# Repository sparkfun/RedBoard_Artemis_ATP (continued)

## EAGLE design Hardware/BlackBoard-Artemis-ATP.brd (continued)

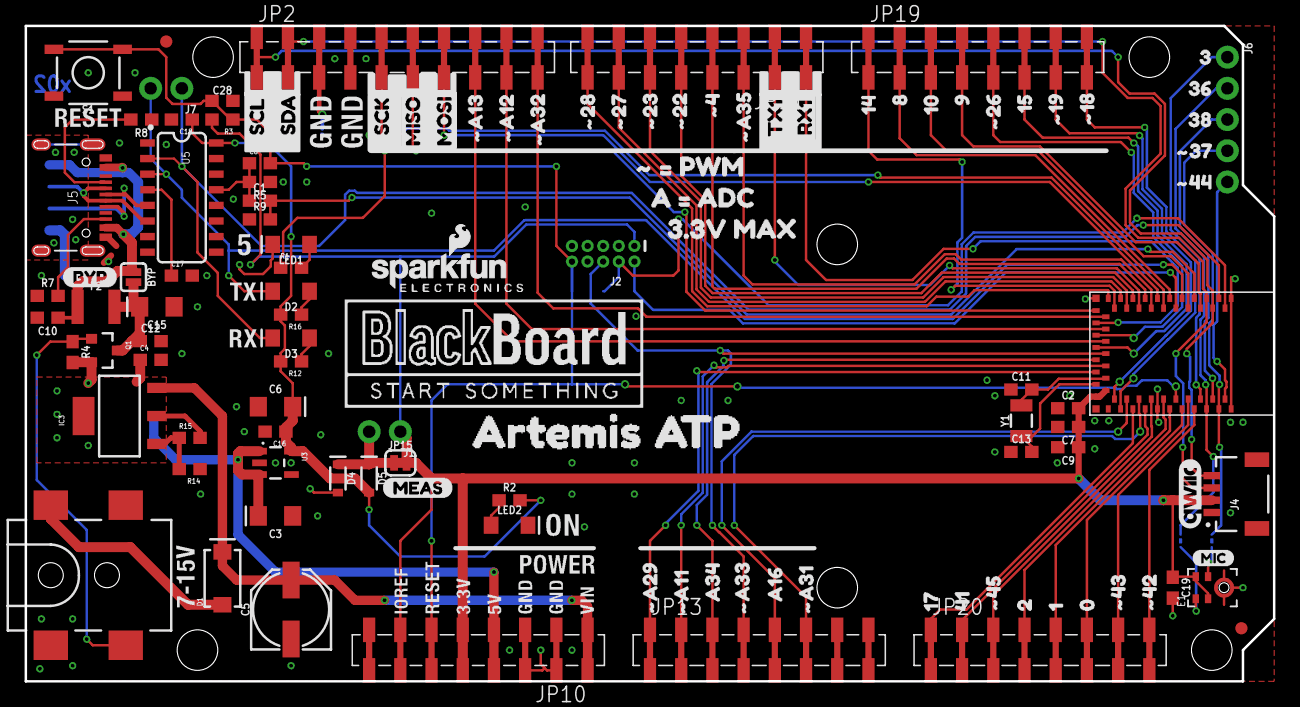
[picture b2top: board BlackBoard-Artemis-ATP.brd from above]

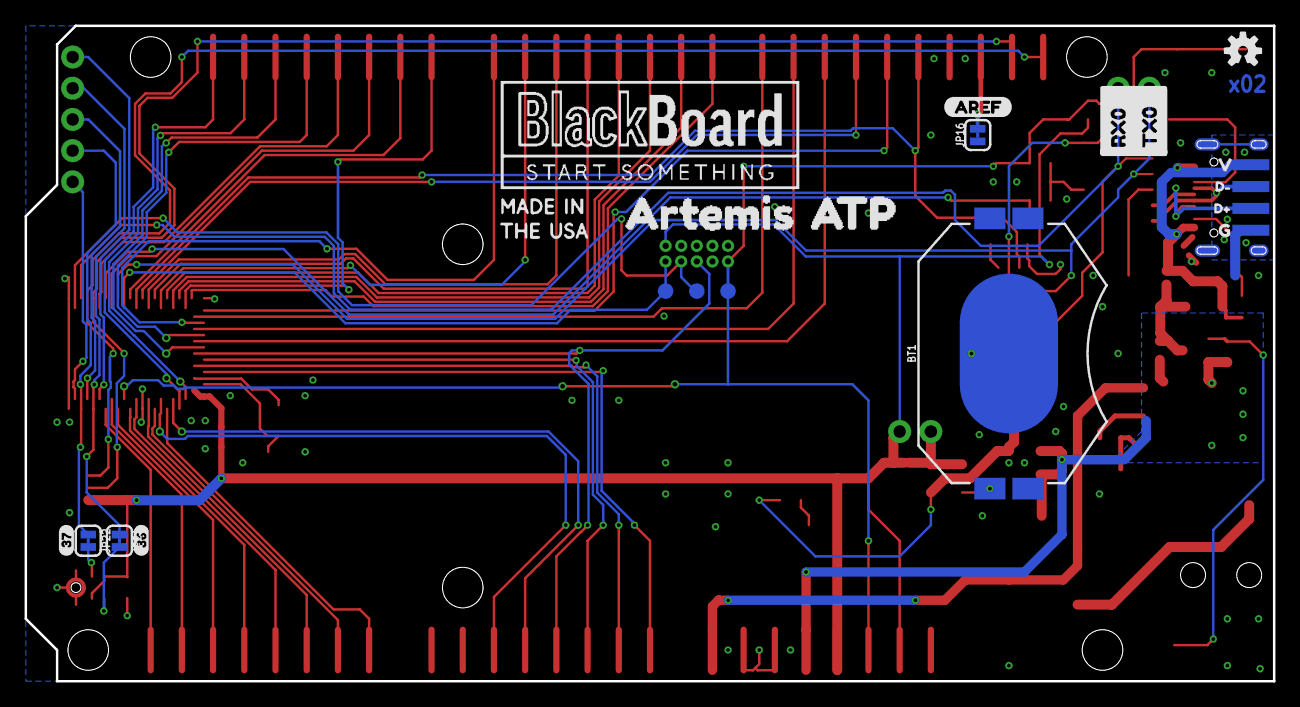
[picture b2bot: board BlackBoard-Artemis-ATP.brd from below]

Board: 2 copper layers, 101.6 x 53.3 mm, 149 parts (23 on the bottom side), 77 nets.

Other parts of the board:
JP17, JP18: STAND-OFF
U$1, U$3: BLACKBOARDLOGO#PNG
U$2: D#3
U$4: MADEINUSA#PNG
U$9: QWIIC_COPYRIGHT_SMALL
U$10: D#4
U$11: G1
U$12: V0
U$13: #A332
U$14, U$15: ARTEMIS0
U$17: A160
U$18: SCL1
U$19: #48
U$20: AREF2
U$21: #229
U$22: SDA0
U$23: #3711
U$24: #187
U$25: #2310
U$26: #2711
U$27: #2812
U$28, U$61: ATP1
U$29: #A113
U$30: #A294
U$31: #A310
U$32: #196
U$33: #A357
U$34: #A1214
U$35: #A1315
U$36: #A3213
U$37: #264
U$38: A342
U$39: #4213
U$40: #4314
U$41: #4412
U$42: #4518
U$43: 015
U$44: 38
U$45: 81
U$46: 93
U$47: MISO8
U$48: MOSI7
U$49: RX01
U$50: SCK9
U$51: 102
U$52: 116
U$53: TX00
U$54: 140
U$55: 155
U$56: 217
U$57: 369
U$58: 1720
U$59: 3810
U$60: 4119
U$62: MIC0
U$63: 364
U$64: 373
U$66: #_#_PWM7
U$67: 3#3V_MAX2
U$68: BYP0
U$69: A_#_ADC6
U$70: MEAS3
U$71: RX11
U$72: TX10

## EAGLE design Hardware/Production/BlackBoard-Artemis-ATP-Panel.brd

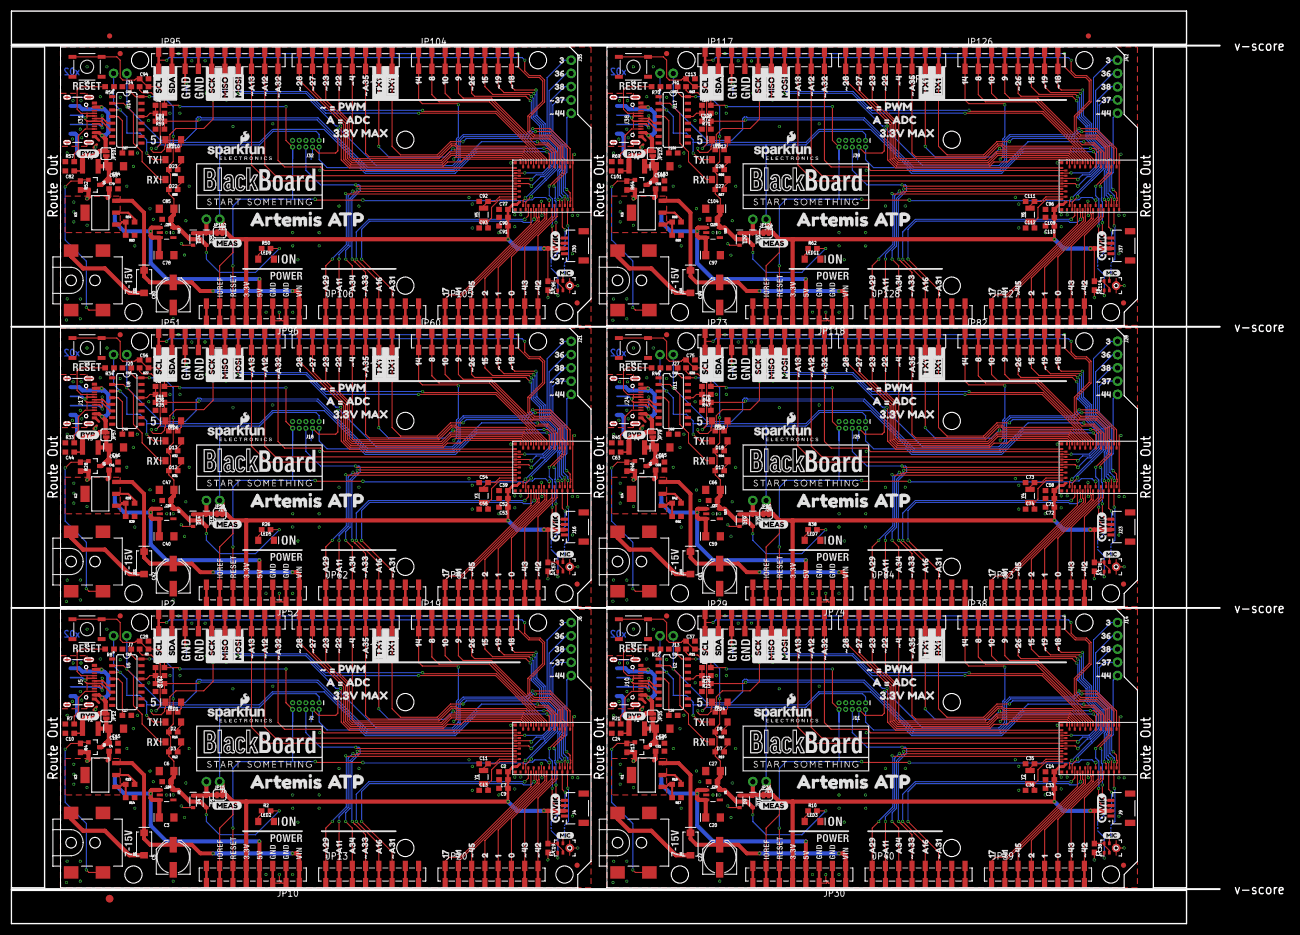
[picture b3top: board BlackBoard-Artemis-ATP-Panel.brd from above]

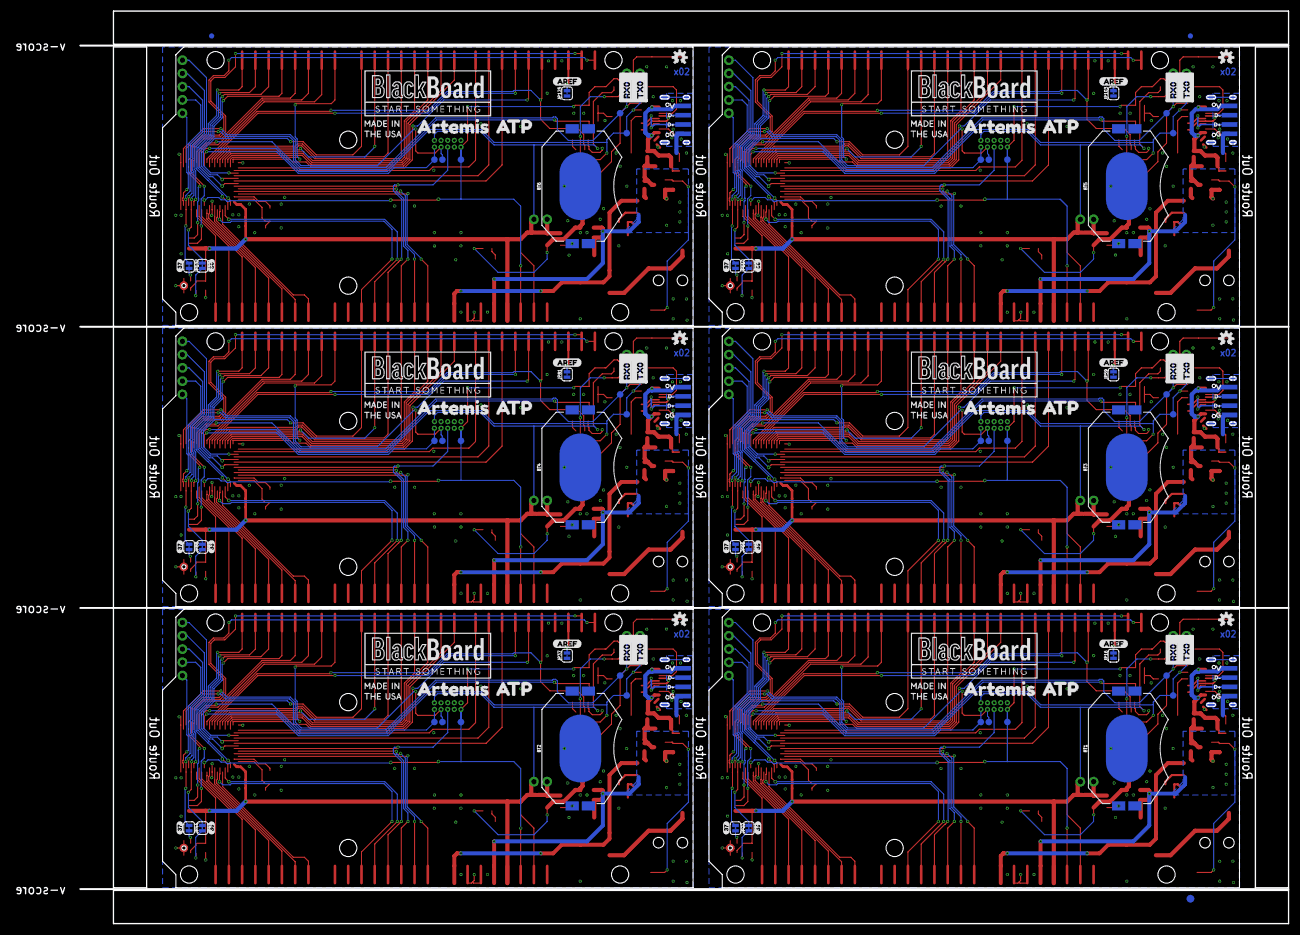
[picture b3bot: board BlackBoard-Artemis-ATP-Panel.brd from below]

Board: 2 copper layers, 244.6 x 174.6 mm, 906 parts (153 on the bottom side), 462 nets.

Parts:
BT1, BT2, BT3, BT4, BT5, BT6: CR2032; BATTCON_20MM_4LEGS_OVERPASTE
C1, C32, C51, C70, C89, C108: 2.2uF; 0603
C2, C4, C8, C10, C12, C14, C18, C19, C21, C23, C24, C25, C31, C38, C39, C41, C43, C44, C45, C50, C57, C58, C60, C62, C63, C64, C69, C76, C77, C79, C81, C82, C83, C88, C95, C96, C98, C100, C101, C102, C107, C114: 0.1uF; 0603
C3, C6, C15, C20, C26, C27, C40, C46, C47, C59, C65, C66, C78, C84, C85, C97, C103, C104: 10uF; EIA3216
C5, C22, C42, C61, C80, C99: 47uF; PANASONIC_D
C7, C33, C52, C71, C90, C109: 10uF; 0603
C9, C16, C29, C34, C48, C53, C67, C72, C86, C91, C105, C110: 1.0uF; 0603
C11, C13, C35, C36, C54, C55, C73, C74, C92, C93, C111, C112: 15pF; 0603
C17, C30, C49, C68, C87, C106: 10nF; 0603
C28, C37, C56, C75, C94, C113: 1nF; 0603
D1, D6, D11, D16, D21, D26: 1A/40V/500mV; SMA-DIODE
D2, D8, D13, D18, D23, D28: GREEN; LED-1206
D3, D7, D12, D17, D22, D27: Yellow; LED-1206
D4, D5, D9, D10, D14, D15, D19, D20, D24, D25, D29, D30: 1A/23V/620mV; SOD-323
E1, E2, E3, E4, E5, E6: SPH0641LM4H-1; SPH0641LM4H-1_MICROPHONE
E$1, E$2, E$3, E$4: FIDUCIAL-1X2
E$5, E$6: FIDUCIAL-1.5X3
F1, F2, F3, F4, F5, F6: 6V/2A; 1210
FRAME1, FRAME2, FRAME3, FRAME4, FRAME5, FRAME6: FRAME-LETTERNO_PACKAGE; DUMMY
IC1, IC2, IC3, IC4, IC5, IC6: LM1117; SOT223-ALT1
J1, J7, J12, J13, J19, J20, J26, J27, J33, J34, J40, J41: 1X02_NO_SILK
J2, J11, J18, J25, J32, J39: CORTEX_DEBUG; 2X5-PTH-1.27MM-NO_SILK
J3, J8, J15, J22, J29, J36: POWER_JACKTOE; POWER_JACK_SMD_OVERPASTE_TOE
J4, J9, J16, J23, J30, J37: JST04_1MM_RA
J5, J10, J17, J24, J31, J38: USB-C; USB-C-16P
J6, J14, J21, J28, J35, J42: 1X05_NO_SILK
JP1, JP31, JP53, JP75, JP97, JP119: SFE_LOGO_NAME.1_INCH; SFE_LOGO_NAME_.1
JP2, JP29, JP51, JP73, JP95, JP117: M10SMD_COMBO; 1X10_SMD_COMBINED
JP3, JP4, JP5, JP6, JP17, JP18, JP23, JP24, JP25, JP26, JP41, JP42, JP45, JP46, JP47, JP48, JP63, JP64, JP67, JP68, JP69, JP70, JP85, JP86, JP89, JP90, JP91, JP92, JP107, JP108, JP111, JP112, JP113, JP114, JP129, JP130: STAND-OFF
JP7, JP32, JP54, JP76, JP98, JP120: SFE_LOGO_FLAME.1_INCH; SFE_LOGO_FLAME_.1
JP8, JP9, JP27, JP28, JP49, JP50, JP71, JP72, JP93, JP94, JP115, JP116: FIDUCIAL1X2; FIDUCIAL-1X2
JP10, JP30, JP52, JP74, JP96, JP118: 1X08_SMD_COMBINED
JP11, JP13, JP19, JP20, JP33, JP38, JP39, JP40, JP55, JP60, JP61, JP62, JP77, JP82, JP83, JP84, JP99, JP104, JP105, JP106, JP121, JP126, JP127, JP128: JP11; 1X08_SMD_COMBINED
JP12, JP35, JP57, JP79, JP101, JP123: SMT-JUMPER_2_NO_SILK
JP14, JP34, JP56, JP78, JP100, JP122: USB_SOLDER_PADS; USB-SOLDER-PADS
JP15, JP16, JP21, JP22, JP36, JP37, JP43, JP44, JP58, JP59, JP65, JP66, JP80, JP81, JP87, JP88, JP102, JP103, JP109, JP110, JP124, JP125, JP131, JP132: SMT-JUMPER_2_NC_TRACE_SILK
LED1, LED4, LED6, LED8, LED10, LED12: BLUE; LED-1206
LED2, LED3, LED5, LED7, LED9, LED11: GREEN; LED-1206
Q1, Q2, Q3, Q4, Q5, Q6: 1.1A/60V/600mΩ; SOT23-3
R1, R6, R12, R16, R19, R20, R25, R31, R32, R37, R43, R44, R49, R55, R56, R61, R67, R68: 4.7k; 0603
R2, R4, R9, R10, R13, R23, R26, R28, R35, R38, R40, R47, R50, R52, R59, R62, R64, R71: 10k; 0603
R3, R5, R11, R24, R27, R36, R39, R48, R51, R60, R63, R72: 100k; 0603
R7, R8, R21, R22, R33, R34, R45, R46, R57, R58, R69, R70: 5.1k; 0603
R14, R17, R29, R41, R53, R65: 715; 0603
R15, R18, R30, R42, R54, R66: 240; 0603
S1, S2, S3, S4, S5, S6: TACTILE_SWITCH_SMD_5.2MM
TP1, TP2, TP3, TP4, TP7, TP10, TP11, TP12, TP15, TP16, TP17, TP20, TP21, TP22, TP25, TP26, TP27, TP30: PAD.03X.05
TP5, TP6, TP8, TP9, TP13, TP14, TP18, TP19, TP23, TP24, TP28, TP29: TEST-POINT3X5; PAD.03X.05
U1, U3, U7, U10, U13, U16: AP2112-3.3V; SOT23-5
U2, U5, U8, U11, U14, U17: CH340C; SO016
U4, U6, U9, U12, U15, U18: ARTEMIS_MODULESMD; ARTEMIS_FP
U$1, U$3, U$6, U$7, U$136, U$137, U$203, U$204, U$270, U$271, U$337, U$338: BLACKBOARDLOGO#PNG
U$2, U$75, U$142, U$209, U$276, U$343: D#3
U$4, U$8, U$138, U$205, U$272, U$339: MADEINUSA#PNG
U$5, U$16, U$135, U$202, U$269, U$336: OSHW-LOGOS; OSHW-LOGO-S
U$9, U$65, U$139, U$206, U$273, U$340: QWIIC_COPYRIGHT_SMALL
U$10, U$76, U$143, U$210, U$277, U$344: D#4
U$11, U$73, U$140, U$207, U$274, U$341: G1
U$12, U$74, U$141, U$208, U$275, U$342: V0
U$13, U$133, U$200, U$267, U$334, U$401: #A332
U$14, U$15, U$77, U$78, U$144, U$145, U$211, U$212, U$278, U$279, U$345, U$346: ARTEMIS0
U$17, U$79, U$146, U$213, U$280, U$347: A160
U$18, U$105, U$172, U$239, U$306, U$373: SCL1
U$19, U$80, U$147, U$214, U$281, U$348: #48
U$20, U$104, U$171, U$238, U$305, U$372: AREF2
U$21, U$81, U$148, U$215, U$282, U$349: #229
U$22, U$106, U$173, U$240, U$307, U$374: SDA0
U$23, U$110, U$177, U$244, U$311, U$378: #3711
U$24, U$107, U$174, U$241, U$308, U$375: #187
U$25, U$82, U$149, U$216, U$283, U$350: #2310
U$26, U$83, U$150, U$217, U$284, U$351: #2711
U$27, U$84, U$151, U$218, U$285, U$352: #2812
U$28, U$61, U$128, U$134, U$195, U$201, U$262, U$268, U$329, U$335, U$396, U$402: ATP1
U$29, U$85, U$152, U$219, U$286, U$353: #A113
U$30, U$86, U$153, U$220, U$287, U$354: #A294
U$31, U$87, U$154, U$221, U$288, U$355: #A310
U$32, U$108, U$175, U$242, U$309, U$376: #196
U$33, U$88, U$155, U$222, U$289, U$356: #A357
U$34, U$89, U$156, U$223, U$290, U$357: #A1214
U$35, U$90, U$157, U$224, U$291, U$358: #A1315
U$36, U$91, U$158, U$225, U$292, U$359: #A3213
U$37, U$109, U$176, U$243, U$310, U$377: #264
U$38, U$92, U$159, U$226, U$293, U$360: A342
U$39, U$111, U$178, U$245, U$312, U$379: #4213
U$40, U$112, U$179, U$246, U$313, U$380: #4314
U$41, U$113, U$180, U$247, U$314, U$381: #4412
U$42, U$114, U$181, U$248, U$315, U$382: #4518
U$43, U$115, U$182, U$249, U$316, U$383: 015
U$44, U$116, U$183, U$250, U$317, U$384: 38
U$45, U$117, U$184, U$251, U$318, U$385: 81
U$46, U$118, U$185, U$252, U$319, U$386: 93
U$47, U$93, U$160, U$227, U$294, U$361: MISO8
U$48, U$94, U$161, U$228, U$295, U$362: MOSI7
U$49, U$102, U$169, U$236, U$303, U$370: RX01
U$50, U$95, U$162, U$229, U$296, U$363: SCK9
U$51, U$119, U$186, U$253, U$320, U$387: 102
U$52, U$120, U$187, U$254, U$321, U$388: 116
U$53, U$103, U$170, U$237, U$304, U$371: TX00
U$54, U$121, U$188, U$255, U$322, U$389: 140
U$55, U$122, U$189, U$256, U$323, U$390: 155
U$56, U$123, U$190, U$257, U$324, U$391: 217
U$57, U$124, U$191, U$258, U$325, U$392: 369
U$58, U$125, U$192, U$259, U$326, U$393: 1720
U$59, U$126, U$193, U$260, U$327, U$394: 3810
U$60, U$127, U$194, U$261, U$328, U$395: 4119
U$62, U$129, U$196, U$263, U$330, U$397: MIC0
U$63, U$130, U$197, U$264, U$331, U$398: 364
U$64, U$131, U$198, U$265, U$332, U$399: 373
U$66, U$96, U$163, U$230, U$297, U$364: #_#_PWM7
U$67, U$97, U$164, U$231, U$298, U$365: 3#3V_MAX2
U$68, U$132, U$199, U$266, U$333, U$400: BYP0
U$69, U$98, U$165, U$232, U$299, U$366: A_#_ADC6
U$70, U$99, U$166, U$233, U$300, U$367: MEAS3
U$71, U$100, U$167, U$234, U$301, U$368: RX11
U$72, U$101, U$168, U$235, U$302, U$369: TX10
Y1, Y2, Y3, Y4, Y5, Y6: 32.768kHz; CRYSTAL-SMD-3.2X1.5MM

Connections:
3.3V: C6.+, C16.1, C18.1, D5.A, R2.2, R12.2, R16.2, U3.5, U5.16
3.3V1: C27.+, C29.1, C31.1, D10.A, R10.2, R19.2, R20.2, U1.5, U2.16
3.3V2: C47.+, C48.1, C50.1, D15.A, R26.2, R31.2, R32.2, U7.5, U8.16
3.3V3: C66.+, C67.1, C69.1, D20.A, R38.2, R43.2, R44.2, U10.5, U11.16
3.3V4: C85.+, C86.1, C88.1, D25.A, R50.2, R55.2, R56.2, U13.5, U14.16
3.3V5: C104.+, C105.1, C107.1, D30.A, R62.2, R67.2, R68.2, U16.5, U17.16
5V: C3.+, C4.1, IC3.2, IC3.4, JP10.4A, JP10.4B, Q1.2, R4.2, R15.2, U3.1, U3.3
5V1: C20.+, C21.1, IC1.2, IC1.4, JP30.4A, JP30.4B, Q2.2, R13.2, R18.2, U1.1, U1.3
5V2: C40.+, C41.1, IC2.2, IC2.4, JP52.4A, JP52.4B, Q3.2, R28.2, R30.2, U7.1, U7.3
5V3: C59.+, C60.1, IC4.2, IC4.4, JP74.4A, JP74.4B, Q4.2, R40.2, R42.2, U10.1, U10.3
5V4: C78.+, C79.1, IC5.2, IC5.4, JP96.4A, JP96.4B, Q5.2, R52.2, R54.2, U13.1, U13.3
5V5: C97.+, C98.1, IC6.2, IC6.4, JP118.4A, JP118.4B, Q6.2, R64.2, R66.2, U16.1, U16.3
!DTR: C1.1, C8.1, R5.2, U5.13
!DTR1: C23.1, C32.1, R24.2, U2.13
!DTR2: C43.1, C51.1, R36.2, U8.13
!DTR3: C62.1, C70.1, R48.2, U11.13
!DTR4: C81.1, C89.1, R60.2, U14.13
!DTR5: C100.1, C108.1, R72.2, U17.13
!RESET: C8.2, C28.1, J2.10, JP10.6A, JP10.6B, R3.1, S1.3, S1.4, TP3.P$1, U4.~RST
!RESET1: C23.2, C37.1, J11.10, JP30.6A, JP30.6B, R11.1, S2.3, S2.4, TP10.P$1, U6.~RST
!RESET2: C43.2, C56.1, J18.10, JP52.6A, JP52.6B, R27.1, S3.3, S3.4, TP15.P$1, U9.~RST
!RESET3: C62.2, C75.1, J25.10, JP74.6A, JP74.6B, R39.1, S4.3, S4.4, TP20.P$1, U12.~RST
!RESET4: C81.2, C94.1, J32.10, JP96.6A, JP96.6B, R51.1, S5.3, S5.4, TP25.P$1, U15.~RST
!RESET5: C100.2, C113.1, J39.10, JP118.6A, JP118.6B, R63.1, S6.3, S6.4, TP30.P$1, U18.~RST
AD1: JP40.5A, JP40.5B, U6.AD16
AD2: JP40.3A, JP40.3B, U6.AD34
AD3: JP62.5A, JP62.5B, U9.AD16
AD4: JP62.3A, JP62.3B, U9.AD34
AD5: JP84.5A, JP84.5B, U12.AD16
AD6: JP84.3A, JP84.3B, U12.AD34
AD7: JP106.5A, JP106.5B, U15.AD16
AD8: JP106.3A, JP106.3B, U15.AD34
AD9: JP128.5A, JP128.5B, U18.AD16
AD10: JP128.3A, JP128.3B, U18.AD34
AD16: JP13.5A, JP13.5B, U4.AD16
AD34: JP13.3A, JP13.3B, U4.AD34
BOOT: C1.2, R9.2, U4.BOOT
BOOT1: C32.2, R23.2, U6.BOOT
BOOT2: C51.2, R35.2, U9.BOOT
BOOT3: C70.2, R47.2, U12.BOOT
BOOT4: C89.2, R59.2, U15.BOOT
BOOT5: C108.2, R71.2, U18.BOOT
CC1: J5.A5, R8.2
CC2: J5.B5, R7.2
CC3: J10.B5, R21.2
CC4: J10.A5, R22.2
CC5: J17.B5, R33.2
CC6: J17.A5, R34.2
CC7: J24.B5, R45.2
CC8: J24.A5, R46.2
CC9: J31.B5, R57.2
CC10: J31.A5, R58.2
CC11: J38.B5, R69.2
CC12: J38.A5, R70.2
D0: JP20.6A, JP20.6B, U4.D0
D1: JP20.5A, JP20.5B, U4.D1
D2: JP20.4A, JP20.4B, U4.D2
D3: J6.1, U4.D3
D4: J14.3, U6.D38
D5: J14.2, JP43.1, U6.D36
D6: JP38.1A, JP38.1B, U6.D14
D7: JP38.2A, JP38.2B, U6.D8
D8: JP19.2A, JP19.2B, U4.D8
D9: JP19.4A, JP19.4B, U4.D9
D10: JP19.3A, JP19.3B, U4.D10
D11: JP38.3A, JP38.3B, U6.D10
D12: JP38.4A, JP38.4B, U6.D9
D13: JP38.6A, JP38.6B, U6.D15
D14: JP19.1A, JP19.1B, U4.D14
D15: JP19.6A, JP19.6B, U4.D15
D16: JP39.1A, JP39.1B, U6.D17
D17: JP20.1A, JP20.1B, U4.D17
D18: JP39.2A, JP39.2B, U6.D41
D19: JP39.4A, JP39.4B, U6.D2
D20: JP39.5A, JP39.5B, U6.D1
D21: JP39.6A, JP39.6B, U6.D0
D22: J14.1, U6.D3
D23: J21.3, U9.D38
D24: J21.2, JP65.1, U9.D36
D25: JP60.1A, JP60.1B, U9.D14
D26: JP60.2A, JP60.2B, U9.D8
D27: JP60.3A, JP60.3B, U9.D10
D28: JP60.4A, JP60.4B, U9.D9
D29: JP60.6A, JP60.6B, U9.D15
D30: JP61.1A, JP61.1B, U9.D17
D31: JP61.2A, JP61.2B, U9.D41
D32: JP61.4A, JP61.4B, U9.D2
D33: JP61.5A, JP61.5B, U9.D1
D34: JP61.6A, JP61.6B, U9.D0
D35: J21.1, U9.D3
D36: J6.2, JP21.1, U4.D36
D37: J28.3, U12.D38
D38: J6.3, U4.D38
D39: J28.2, JP87.1, U12.D36
D40: JP82.1A, JP82.1B, U12.D14
D40/SDA: J4.3, JP2.2A, JP2.2B, U4.D40
D40/SDA1: J9.3, JP29.2A, JP29.2B, U6.D40
D40/SDA2: J16.3, JP51.2A, JP51.2B, U9.D40
D40/SDA3: J23.3, JP73.2A, JP73.2B, U12.D40
D40/SDA4: J30.3, JP95.2A, JP95.2B, U15.D40
D40/SDA5: J37.3, JP117.2A, JP117.2B, U18.D40
D41: JP20.2A, JP20.2B, U4.D41
D42: JP82.2A, JP82.2B, U12.D8
D43: JP82.3A, JP82.3B, U12.D10
D44: JP82.4A, JP82.4B, U12.D9
D45: JP82.6A, JP82.6B, U12.D15
D46: JP83.1A, JP83.1B, U12.D17
D47: JP83.2A, JP83.2B, U12.D41
D48: JP83.4A, JP83.4B, U12.D2
D49: JP83.5A, JP83.5B, U12.D1
D50: JP83.6A, JP83.6B, U12.D0
D51: J28.1, U12.D3
D52: J35.3, U15.D38
D53: J35.2, JP109.1, U15.D36
D54: JP104.1A, JP104.1B, U15.D14
D55: JP104.2A, JP104.2B, U15.D8
D56: JP104.3A, JP104.3B, U15.D10
D57: JP104.4A, JP104.4B, U15.D9
D58: JP104.6A, JP104.6B, U15.D15
D59: JP105.1A, JP105.1B, U15.D17
D60: JP105.2A, JP105.2B, U15.D41
D61: JP105.4A, JP105.4B, U15.D2
D62: JP105.5A, JP105.5B, U15.D1
D63: JP105.6A, JP105.6B, U15.D0
D64: J35.1, U15.D3
D65: J42.3, U18.D38
D66: J42.2, JP131.1, U18.D36
D67: JP126.1A, JP126.1B, U18.D14
D68: JP126.2A, JP126.2B, U18.D8
D69: JP126.3A, JP126.3B, U18.D10
D70: JP126.4A, JP126.4B, U18.D9
D71: JP126.6A, JP126.6B, U18.D15
D72: JP127.1A, JP127.1B, U18.D17
D73: JP127.2A, JP127.2B, U18.D41
D74: JP127.4A, JP127.4B, U18.D2
D75: JP127.5A, JP127.5B, U18.D1
D76: JP127.6A, JP127.6B, U18.D0
D77: J42.1, U18.D3
D+: J5.A6, J5.B6, JP14.D+, U5.5
D+1: J10.A6, J10.B6, JP34.D+, U2.5
D+2: J17.A6, J17.B6, JP56.D+, U8.5
D+3: J24.A6, J24.B6, JP78.D+, U11.5
D+4: J31.A6, J31.B6, JP100.D+, U14.5
D+5: J38.A6, J38.B6, JP122.D+, U17.5
D-: J5.A7, J5.B7, JP14.D-, U5.6
D-1: J10.A7, J10.B7, JP34.D-, U2.6
D-2: J17.A7, J17.B7, JP56.D-, U8.6
D-3: J24.A7, J24.B7, JP78.D-, U11.6
D-4: J31.A7, J31.B7, JP100.D-, U14.6
D-5: J38.A7, J38.B7, JP122.D-, U17.6
GND: BT1.2, C2.1, C3.-, C4.2, C5.-, C6.-, C7.2, C9.2, C10.2, C11.1, C12.2, C13.1, C15.-, C16.2, C17.2, C18.2, C19.2, C28.2, E1.3, E1.6, E1.7, E1.8, J2.3, J2.5, J2.9, J3.GND, J4.1, J5.GND, J5.GND2, JP2.4A, JP2.4B, JP10.2A, JP10.2B, JP10.3A, JP10.3B, JP14.GND, JP16.1, LED1.C, LED2.C, R5.1, R7.1, R8.1, R9.1, R14.1, S1.1, S1.2, U3.2, U4.GND@1, U4.GND@22, U4.GND@38, U4.GND@39, U4.GND@47, U4.GND@59, U5.1
GND1: BT2.2, C14.1, C20.-, C21.2, C22.-, C24.2, C25.2, C26.-, C27.-, C29.2, C30.2, C31.2, C33.2, C34.2, C35.1, C36.1, C37.2, C38.2, E2.3, E2.6, E2.7, E2.8, J8.GND, J9.1, J10.GND, J10.GND2, J11.3, J11.5, J11.9, JP29.4A, JP29.4B, JP30.2A, JP30.2B, JP30.3A, JP30.3B, JP34.GND, JP37.1, LED3.C, LED4.C, R17.1, R21.1, R22.1, R23.1, R24.1, S2.1, S2.2, U1.2, U2.1, U6.GND@1, U6.GND@22, U6.GND@38, U6.GND@39, U6.GND@47, U6.GND@59
GND2: BT3.2, C39.1, C40.-, C41.2, C42.-, C44.2, C45.2, C46.-, C47.-, C48.2, C49.2, C50.2, C52.2, C53.2, C54.1, C55.1, C56.2, C57.2, E3.3, E3.6, E3.7, E3.8, J15.GND, J16.1, J17.GND, J17.GND2, J18.3, J18.5, J18.9, JP51.4A, JP51.4B, JP52.2A, JP52.2B, JP52.3A, JP52.3B, JP56.GND, JP59.1, LED5.C, LED6.C, R29.1, R33.1, R34.1, R35.1, R36.1, S3.1, S3.2, U7.2, U8.1, U9.GND@1, U9.GND@22, U9.GND@38, U9.GND@39, U9.GND@47, U9.GND@59
GND3: BT4.2, C58.1, C59.-, C60.2, C61.-, C63.2, C64.2, C65.-, C66.-, C67.2, C68.2, C69.2, C71.2, C72.2, C73.1, C74.1, C75.2, C76.2, E4.3, E4.6, E4.7, E4.8, J22.GND, J23.1, J24.GND, J24.GND2, J25.3, J25.5, J25.9, JP73.4A, JP73.4B, JP74.2A, JP74.2B, JP74.3A, JP74.3B, JP78.GND, JP81.1, LED7.C, LED8.C, R41.1, R45.1, R46.1, R47.1, R48.1, S4.1, S4.2, U10.2, U11.1, U12.GND@1, U12.GND@22, U12.GND@38, U12.GND@39, U12.GND@47, U12.GND@59
GND4: BT5.2, C77.1, C78.-, C79.2, C80.-, C82.2, C83.2, C84.-, C85.-, C86.2, C87.2, C88.2, C90.2, C91.2, C92.1, C93.1, C94.2, C95.2, E5.3, E5.6, E5.7, E5.8, J29.GND, J30.1, J31.GND, J31.GND2, J32.3, J32.5, J32.9, JP95.4A, JP95.4B, JP96.2A, JP96.2B, JP96.3A, JP96.3B, JP100.GND, JP103.1, LED9.C, LED10.C, R53.1, R57.1, R58.1, R59.1, R60.1, S5.1, S5.2, U13.2, U14.1, U15.GND@1, U15.GND@22, U15.GND@38, U15.GND@39, U15.GND@47, U15.GND@59
GND5: BT6.2, C96.1, C97.-, C98.2, C99.-, C101.2, C102.2, C103.-, C104.-, C105.2, C106.2, C107.2, C109.2, C110.2, C111.1, C112.1, C113.2, C114.2, E6.3, E6.6, E6.7, E6.8, J36.GND, J37.1, J38.GND, J38.GND2, J39.3, J39.5, J39.9, JP117.4A, JP117.4B, JP118.2A, JP118.2B, JP118.3A, JP118.3B, JP122.GND, JP125.1, LED11.C, LED12.C, R65.1, R69.1, R70.1, R71.1, R72.1, S6.1, S6.2, U16.2, U17.1, U18.GND@1, U18.GND@22, U18.GND@38, U18.GND@39, U18.GND@47, U18.GND@59
INSERT: J3.P$4, Q1.1, R4.1
INSERT1: J8.P$4, Q2.1, R13.1
INSERT2: J15.P$4, Q3.1, R28.1
INSERT3: J22.P$4, Q4.1, R40.1
INSERT4: J29.P$4, Q5.1, R52.1
INSERT5: J36.P$4, Q6.1, R64.1
unnamed: LED1.A, R1.2
unnamed: LED2.A, R2.1
unnamed: D4.C, D5.C, J1.2, JP15.1
unnamed: D2.A, R16.1
unnamed: C17.1, U5.4
unnamed: C11.2, U4.XO, Y1.P$2
unnamed: C13.2, U4.XI, Y1.P$1
unnamed: D3.A, R12.1
unnamed: JP2.3A, JP2.3B, JP16.2
unnamed: LED3.A, R10.1
unnamed: LED4.A, R6.2
unnamed: IC1.1, R17.2, R18.1
unnamed: D8.A, R20.1
unnamed: IC3.1, R14.2, R15.1
unnamed: D7.A, R19.1
unnamed: C30.1, U2.4
unnamed: D9.C, D10.C, J12.2, JP36.1
unnamed: C35.2, U6.XO, Y2.P$2
unnamed: C36.2, U6.XI, Y2.P$1
unnamed: JP29.3A, JP29.3B, JP37.2
unnamed: LED5.A, R26.1
unnamed: LED6.A, R25.2
unnamed: IC2.1, R29.2, R30.1
unnamed: D13.A, R32.1
unnamed: D12.A, R31.1
unnamed: C49.1, U8.4
unnamed: D14.C, D15.C, J19.2, JP58.1
unnamed: C54.2, U9.XO, Y3.P$2
unnamed: C55.2, U9.XI, Y3.P$1
unnamed: JP51.3A, JP51.3B, JP59.2
unnamed: LED7.A, R38.1
unnamed: LED8.A, R37.2
unnamed: IC4.1, R41.2, R42.1
unnamed: D18.A, R44.1
unnamed: D17.A, R43.1
unnamed: C68.1, U11.4
unnamed: D19.C, D20.C, J26.2, JP80.1
unnamed: C73.2, U12.XO, Y4.P$2
unnamed: C74.2, U12.XI, Y4.P$1
unnamed: JP73.3A, JP73.3B, JP81.2
unnamed: LED9.A, R50.1
unnamed: LED10.A, R49.2
unnamed: IC5.1, R53.2, R54.1
unnamed: D23.A, R56.1
unnamed: D22.A, R55.1
unnamed: C87.1, U14.4
unnamed: D24.C, D25.C, J33.2, JP102.1
unnamed: C92.2, U15.XO, Y5.P$2
unnamed: C93.2, U15.XI, Y5.P$1
unnamed: JP95.3A, JP95.3B, JP103.2
unnamed: LED11.A, R62.1
unnamed: LED12.A, R61.2
unnamed: IC6.1, R65.2, R66.1
unnamed: D28.A, R68.1
unnamed: D27.A, R67.1
unnamed: C106.1, U17.4
unnamed: D29.C, D30.C, J40.2, JP124.1
unnamed: C111.2, U18.XO, Y6.P$2
unnamed: C112.2, U18.XI, Y6.P$1
unnamed: JP117.3A, JP117.3B, JP125.2
PDMCLK: E1.4, JP22.2
PDMCLK1: E2.4, JP44.2
PDMCLK2: E3.4, JP66.2
PDMCLK3: E4.4, JP88.2
PDMCLK4: E5.4, JP110.2
PDMCLK5: E6.4, JP132.2
PDMDATA: E1.1, JP21.2
PDMDATA1: E2.1, JP43.2
PDMDATA2: E3.1, JP65.2
PDMDATA3: E4.1, JP87.2
PDMDATA4: E5.1, JP109.2
PDMDATA5: E6.1, JP131.2
PWRIN: D1.A, J3.VIN0
PWRIN1: D6.A, J8.VIN0
PWRIN2: D11.A, J15.VIN0
PWRIN3: D16.A, J22.VIN0
PWRIN4: D21.A, J29.VIN0
PWRIN5: D26.A, J36.VIN0
RXI-0: D3.C, J7.1, TP5.P$1, U4.RXI-0, U5.2
RXI-1: D7.C, J13.1, TP8.P$1, U2.2, U6.RXI-0
RXI-2: D12.C, J20.1, TP13.P$1, U8.2, U9.RXI-0
RXI-3: D17.C, J27.1, TP18.P$1, U11.2, U12.RXI-0
RXI-4: D22.C, J34.1, TP23.P$1, U14.2, U15.RXI-0
RXI-5: D27.C, J41.1, TP28.P$1, U17.2, U18.RXI-0
SHLD: J5.SHLD1, J5.SHLD2, J5.SHLD3, J5.SHLD4, J5.SHLD5, J5.SHLD6, J5.SHLD7, J5.SHLD8
SHLD1: J10.SHLD1, J10.SHLD2, J10.SHLD3, J10.SHLD4, J10.SHLD5, J10.SHLD6, J10.SHLD7, J10.SHLD8
SHLD2: J17.SHLD1, J17.SHLD2, J17.SHLD3, J17.SHLD4, J17.SHLD5, J17.SHLD6, J17.SHLD7, J17.SHLD8
SHLD3: J24.SHLD1, J24.SHLD2, J24.SHLD3, J24.SHLD4, J24.SHLD5, J24.SHLD6, J24.SHLD7, J24.SHLD8
SHLD4: J31.SHLD1, J31.SHLD2, J31.SHLD3, J31.SHLD4, J31.SHLD5, J31.SHLD6, J31.SHLD7, J31.SHLD8
SHLD5: J38.SHLD1, J38.SHLD2, J38.SHLD3, J38.SHLD4, J38.SHLD5, J38.SHLD6, J38.SHLD7, J38.SHLD8
SWDCK: J2.4, TP1.P$1, U4.SWDCK
SWDCK1: J11.4, TP4.P$1, U6.SWDCK
SWDCK2: J18.4, TP11.P$1, U9.SWDCK
SWDCK3: J25.4, TP16.P$1, U12.SWDCK
SWDCK4: J32.4, TP21.P$1, U15.SWDCK
SWDCK5: J39.4, TP26.P$1, U18.SWDCK
SWDIO: J2.2, TP2.P$1, U4.SWDIO
SWDIO1: J11.2, TP7.P$1, U6.SWDIO
SWDIO2: J18.2, TP12.P$1, U9.SWDIO
SWDIO3: J25.2, TP17.P$1, U12.SWDIO
SWDIO4: J32.2, TP22.P$1, U15.SWDIO
SWDIO5: J39.2, TP27.P$1, U18.SWDIO
TXO-0: D2.C, J7.2, TP6.P$1, U4.TXO-0, U5.3
TXO-1: D8.C, J13.2, TP9.P$1, U2.3, U6.TXO-0
TXO-2: D13.C, J20.2, TP14.P$1, U8.3, U9.TXO-0
TXO-3: D18.C, J27.2, TP19.P$1, U11.3, U12.TXO-0
TXO-4: D23.C, J34.2, TP24.P$1, U14.3, U15.TXO-0
TXO-5: D28.C, J41.2, TP29.P$1, U17.3, U18.TXO-0
USBVCC: C12.1, C15.+, F2.2, JP12.2, Q1.3
USBVCC1: C25.1, C26.+, F1.2, JP35.2, Q2.3
USBVCC2: C45.1, C46.+, F3.2, JP57.2, Q3.3
USBVCC3: C64.1, C65.+, F4.2, JP79.2, Q4.3
USBVCC4: C83.1, C84.+, F5.2, JP101.2, Q5.3
USBVCC5: C102.1, C103.+, F6.2, JP123.2, Q6.3
VDD: C2.2, C7.1, C9.1, C19.1, E1.2, E1.5, J1.1, J2.1, J4.2, JP10.5A, JP10.5B, JP10.7A, JP10.7B, JP15.2, R3.2, U4.VDD@36, U4.VDD@37
VDD1: C14.2, C33.1, C34.1, C38.1, E2.2, E2.5, J9.2, J11.1, J12.1, JP30.5A, JP30.5B, JP30.7A, JP30.7B, JP36.2, R11.2, U6.VDD@36, U6.VDD@37
VDD2: C39.2, C52.1, C53.1, C57.1, E3.2, E3.5, J16.2, J18.1, J19.1, JP52.5A, JP52.5B, JP52.7A, JP52.7B, JP58.2, R27.2, U9.VDD@36, U9.VDD@37
VDD3: C58.2, C71.1, C72.1, C76.1, E4.2, E4.5, J23.2, J25.1, J26.1, JP74.5A, JP74.5B, JP74.7A, JP74.7B, JP80.2, R39.2, U12.VDD@36, U12.VDD@37
VDD4: C77.2, C90.1, C91.1, C95.1, E5.2, E5.5, J30.2, J32.1, J33.1, JP96.5A, JP96.5B, JP96.7A, JP96.7B, JP102.2, R51.2, U15.VDD@36, U15.VDD@37
VDD5: C96.2, C109.1, C110.1, C114.1, E6.2, E6.5, J37.2, J39.1, J40.1, JP118.5A, JP118.5B, JP118.7A, JP118.7B, JP124.2, R63.2, U18.VDD@36, U18.VDD@37
VIN: C5.+, D1.C, IC3.3, JP10.1A, JP10.1B
VIN1: C22.+, D6.C, IC1.3, JP30.1A, JP30.1B
VIN2: C42.+, D11.C, IC2.3, JP52.1A, JP52.1B
VIN3: C61.+, D16.C, IC4.3, JP74.1A, JP74.1B
VIN4: C80.+, D21.C, IC5.3, JP96.1A, JP96.1B
VIN5: C99.+, D26.C, IC6.3, JP118.1A, JP118.1B
VUSB: C10.1, F2.1, J5.VBUS1, J5.VBUS2, JP12.1, JP14.VBUS
VUSB1: C24.1, F1.1, J10.VBUS1, J10.VBUS2, JP34.VBUS, JP35.1
VUSB2: C44.1, F3.1, J17.VBUS1, J17.VBUS2, JP56.VBUS, JP57.1
VUSB3: C63.1, F4.1, J24.VBUS1, J24.VBUS2, JP78.VBUS, JP79.1
VUSB4: C82.1, F5.1, J31.VBUS1, J31.VBUS2, JP100.VBUS, JP101.1
VUSB5: C101.1, F6.1, J38.VBUS1, J38.VBUS2, JP122.VBUS, JP123.1
V_BATT: BT1.1, D4.A
V_BATT1: BT2.1, D9.A
V_BATT2: BT3.1, D14.A
V_BATT3: BT4.1, D19.A
V_BATT4: BT5.1, D24.A
V_BATT5: BT6.1, D29.A
~AD1: JP40.6A, JP40.6B, U6.~AD31
~AD2: JP40.1A, JP40.1B, U6.~AD29
~AD3: JP40.2A, JP40.2B, U6.~AD11
~AD4: JP33.3A, JP33.3B, U6.~AD35
~AD5: JP29.10A, JP29.10B, U6.~AD32
~AD6: JP29.9A, JP29.9B, U6.~AD12
~AD7: JP29.8A, JP29.8B, U6.~AD13
~AD8: JP62.6A, JP62.6B, U9.~AD31
~AD9: JP62.1A, JP62.1B, U9.~AD29
~AD10: JP62.2A, JP62.2B, U9.~AD11
~AD11: JP13.2A, JP13.2B, U4.~AD11
~AD12: JP2.9A, JP2.9B, U4.~AD12
~AD13: JP2.8A, JP2.8B, U4.~AD13
~AD14: JP55.3A, JP55.3B, U9.~AD35
~AD15: JP51.10A, JP51.10B, U9.~AD32
~AD16: JP51.9A, JP51.9B, U9.~AD12
~AD17: JP51.8A, JP51.8B, U9.~AD13
~AD18: JP84.6A, JP84.6B, U12.~AD31
~AD19: JP84.1A, JP84.1B, U12.~AD29
~AD20: JP84.2A, JP84.2B, U12.~AD11
~AD21: JP77.3A, JP77.3B, U12.~AD35
~AD22: JP73.10A, JP73.10B, U12.~AD32
~AD23: JP73.9A, JP73.9B, U12.~AD12
~AD24: JP73.8A, JP73.8B, U12.~AD13
~AD25: JP106.6A, JP106.6B, U15.~AD31
~AD26: JP106.1A, JP106.1B, U15.~AD29
~AD27: JP106.2A, JP106.2B, U15.~AD11
~AD28: JP99.3A, JP99.3B, U15.~AD35
~AD29: JP13.1A, JP13.1B, U4.~AD29
~AD30: JP95.10A, JP95.10B, U15.~AD32
~AD31: JP13.6A, JP13.6B, U4.~AD31
~AD32: JP2.10A, JP2.10B, U4.~AD32
~AD33: JP95.9A, JP95.9B, U15.~AD12
~AD33/SWO: J2.6, JP13.4A, JP13.4B, U4.~AD33/SWO
~AD33/SWO1: J11.6, JP40.4A, JP40.4B, U6.~AD33/SWO
~AD33/SWO2: J18.6, JP62.4A, JP62.4B, U9.~AD33/SWO
~AD33/SWO3: J25.6, JP84.4A, JP84.4B, U12.~AD33/SWO
~AD33/SWO4: J32.6, JP106.4A, JP106.4B, U15.~AD33/SWO
~AD33/SWO5: J39.6, JP128.4A, JP128.4B, U18.~AD33/SWO
~AD34: JP95.8A, JP95.8B, U15.~AD13
~AD35: JP11.3A, JP11.3B, U4.~AD35
~AD36: JP128.6A, JP128.6B, U18.~AD31
~AD37: JP128.1A, JP128.1B, U18.~AD29
~AD38: JP128.2A, JP128.2B, U18.~AD11
~AD39: JP121.3A, JP121.3B, U18.~AD35
~AD40: JP117.10A, JP117.10B, U18.~AD32
~AD41: JP117.9A, JP117.9B, U18.~AD12
~AD42: JP117.8A, JP117.8B, U18.~AD13
~D1: JP33.4A, JP33.4B, U6.~D4
~D2: JP33.5A, JP33.5B, U6.~D22
~D3: JP33.6A, JP33.6B, U6.~D23
~D4: JP11.4A, JP11.4B, U4.~D4
~D5: JP33.7A, JP33.7B, U6.~D27
~D5/SCK: JP2.5A, JP2.5B, R1.1, U4.~D5
~D5/SCK1: JP29.5A, JP29.5B, R6.1, U6.~D5
~D5/SCK2: JP51.5A, JP51.5B, R25.1, U9.~D5
~D5/SCK3: JP73.5A, JP73.5B, R37.1, U12.~D5
~D5/SCK4: JP95.5A, JP95.5B, R49.1, U15.~D5
~D5/SCK5: JP117.5A, JP117.5B, R61.1, U18.~D5
~D6: JP33.8A, JP33.8B, U6.~D28
~D6/MISO: JP2.6A, JP2.6B, U4.~D6
~D6/MISO1: JP29.6A, JP29.6B, U6.~D6
~D6/MISO2: JP51.6A, JP51.6B, U9.~D6
~D6/MISO3: JP73.6A, JP73.6B, U12.~D6
~D6/MISO4: JP95.6A, JP95.6B, U15.~D6
~D6/MISO5: JP117.6A, JP117.6B, U18.~D6
~D7: JP39.8A, JP39.8B, U6.~D42
~D7/MOSI: JP2.7A, JP2.7B, U4.D7
~D7/MOSI1: JP29.7A, JP29.7B, U6.D7
~D7/MOSI2: JP51.7A, JP51.7B, U9.D7
~D7/MOSI3: JP73.7A, JP73.7B, U12.D7
~D7/MOSI4: JP95.7A, JP95.7B, U15.D7
~D7/MOSI5: JP117.7A, JP117.7B, U18.D7
~D8: JP39.7A, JP39.7B, U6.~D43
~D9: J14.4, JP44.1, U6.~D37
~D10: JP38.5A, JP38.5B, U6.~D26
~D11: JP38.7A, JP38.7B, U6.~D19
~D12: JP38.8A, JP38.8B, U6.~D18
~D13: JP39.3A, JP39.3B, U6.~D45
~D14: J14.5, U6.~D44
~D15: JP55.4A, JP55.4B, U9.~D4
~D16: JP55.5A, JP55.5B, U9.~D22
~D17: JP55.6A, JP55.6B, U9.~D23
~D18: JP19.8A, JP19.8B, U4.~D18
~D19: JP19.7A, JP19.7B, U4.~D19
~D20: JP55.7A, JP55.7B, U9.~D27
~D21: JP55.8A, JP55.8B, U9.~D28
~D22: JP11.5A, JP11.5B, U4.~D22
~D23: JP11.6A, JP11.6B, U4.~D23
~D24: JP61.8A, JP61.8B, U9.~D42
~D24/TXO-1: JP11.2A, JP11.2B, U4.~D24
~D24/TXO-2: JP33.2A, JP33.2B, U6.~D24
~D24/TXO-3: JP55.2A, JP55.2B, U9.~D24
~D24/TXO-4: JP77.2A, JP77.2B, U12.~D24
~D24/TXO-5: JP99.2A, JP99.2B, U15.~D24
~D24/TXO-6: JP121.2A, JP121.2B, U18.~D24
~D25: JP61.7A, JP61.7B, U9.~D43
~D25/RXI-1: JP11.1A, JP11.1B, U4.~D25
~D25/RXI-2: JP33.1A, JP33.1B, U6.~D25
~D25/RXI-3: JP55.1A, JP55.1B, U9.~D25
~D25/RXI-4: JP77.1A, JP77.1B, U12.~D25
~D25/RXI-5: JP99.1A, JP99.1B, U15.~D25
~D25/RXI-6: JP121.1A, JP121.1B, U18.~D25
~D26: JP19.5A, JP19.5B, U4.~D26
~D27: JP11.7A, JP11.7B, U4.~D27
~D28: JP11.8A, JP11.8B, U4.~D28
~D29: J21.4, JP66.1, U9.~D37
~D30: JP60.5A, JP60.5B, U9.~D26
~D31: JP60.7A, JP60.7B, U9.~D19
~D32: JP60.8A, JP60.8B, U9.~D18
~D33: JP61.3A, JP61.3B, U9.~D45
~D34: J21.5, U9.~D44
~D35: JP77.4A, JP77.4B, U12.~D4
~D36: JP77.5A, JP77.5B, U12.~D22
~D37: J6.4, JP22.1, U4.~D37
~D38: JP77.6A, JP77.6B, U12.~D23
~D39: JP77.7A, JP77.7B, U12.~D27
~D39/SCL: J4.4, JP2.1A, JP2.1B, U4.~D39
~D39/SCL1: J9.4, JP29.1A, JP29.1B, U6.~D39
~D39/SCL2: J16.4, JP51.1A, JP51.1B, U9.~D39
~D39/SCL3: J23.4, JP73.1A, JP73.1B, U12.~D39
~D39/SCL4: J30.4, JP95.1A, JP95.1B, U15.~D39
~D39/SCL5: J37.4, JP117.1A, JP117.1B, U18.~D39
~D40: JP77.8A, JP77.8B, U12.~D28
~D41: JP83.8A, JP83.8B, U12.~D42
~D42: JP20.8A, JP20.8B, U4.~D42
~D43: JP20.7A, JP20.7B, U4.~D43
~D44: J6.5, U4.~D44
~D45: JP20.3A, JP20.3B, U4.~D45
~D46: JP83.7A, JP83.7B, U12.~D43
~D47: J28.4, JP88.1, U12.~D37
~D48: JP82.5A, JP82.5B, U12.~D26
~D49: JP82.7A, JP82.7B, U12.~D19
~D50: JP82.8A, JP82.8B, U12.~D18
~D51: JP83.3A, JP83.3B, U12.~D45
~D52: J28.5, U12.~D44
~D53: JP99.4A, JP99.4B, U15.~D4
~D54: JP99.5A, JP99.5B, U15.~D22
~D55: JP99.6A, JP99.6B, U15.~D23
~D56: JP99.7A, JP99.7B, U15.~D27
~D57: JP99.8A, JP99.8B, U15.~D28
~D58: JP105.8A, JP105.8B, U15.~D42
~D59: JP105.7A, JP105.7B, U15.~D43
~D60: J35.4, JP110.1, U15.~D37
~D61: JP104.5A, JP104.5B, U15.~D26
~D62: JP104.7A, JP104.7B, U15.~D19
~D63: JP104.8A, JP104.8B, U15.~D18
~D64: JP105.3A, JP105.3B, U15.~D45
~D65: J35.5, U15.~D44
~D66: JP121.4A, JP121.4B, U18.~D4
~D67: JP121.5A, JP121.5B, U18.~D22
~D68: JP121.6A, JP121.6B, U18.~D23
~D69: JP121.7A, JP121.7B, U18.~D27
~D70: JP121.8A, JP121.8B, U18.~D28
~D71: JP127.8A, JP127.8B, U18.~D42
~D72: JP127.7A, JP127.7B, U18.~D43
~D73: J42.4, JP132.1, U18.~D37
~D74: JP126.5A, JP126.5B, U18.~D26
~D75: JP126.7A, JP126.7B, U18.~D19
~D76: JP126.8A, JP126.8B, U18.~D18
~D77: JP127.3A, JP127.3B, U18.~D45
~D78: J42.5, U18.~D44

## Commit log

2019-07-01 Remove old files. Rename to RedBoard.
2019-07-02 Add SMD Debug. Add PTH holes to each connector.
2019-07-02 Add silk indicators to PTH pins
2019-07-03 Consolidated to one sch sheet.
2019-07-03 Approved DRC errors
2019-07-03 Adding production panels
2019-07-03 Adding designed by text
2021-02-01 Fix image link
